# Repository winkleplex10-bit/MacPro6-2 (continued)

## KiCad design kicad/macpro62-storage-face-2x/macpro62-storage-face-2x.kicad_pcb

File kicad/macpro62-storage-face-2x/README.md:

# macpro62-storage-face-2x (S2X rev A0): Face S module, 2 x M.2 2280, switchless
Replaces the parked 4-drive ASM2824 board (`../macpro62-storage-face`, SM-1) for the first build. Same outline, holes, J1 MCIO 124 at X 47.0 and bus-bar lugs.

- J1 x8 → x4 slot A (lanes 0-3, REFCLK0/PERST0#) + x4 slot B (lanes 4-7, REFCLK1/PERST1#). Slot B needs host changes: `docs/ICD_CHANGES.md`.
- M.2 M-key: LOTES APCI0107-P001A (LCSC C841661) + SMTSO2030CTJ standoffs (2280).
- Power: TPS259470 eFuse, INA238 (0x40), 2 x TPS54331 buck (3 A per slot), TMP1075 0x48/0x49, M24C64 0x50, activity LEDs D3/D4.
- 4L JLC04161H-7628, 85 Ω pairs; all parts on B (JLC Economic, single-sided).

Checks (2026-10-08): DRC 0 / unconnected 0 / schematic parity 0 (kicad-cli, all severities), ERC 0 (`erc_report.txt`).
Fab/assembly: `jlc/` (gerbers zip, BOM 36 lines, CPL 81 parts, all Bottom). Previews: `docs/preview_2X_*.png`. Log: `PROGRESS.md`.
Deviations D-2X-1 (hot spot), D-2X-2 (data-lane polarity inversion), D-S1 (no X-bracket): `docs/ICD_CHANGES.md`.

Rebuild: tools/model.py → build_pcb.py → route_hs.py → route_pwr.py → s2x_ls.py fan → Freerouting (10 min) → s2x_ls.py import →
s2x_clean.py (loop) → s2x_finish.py → tools/drc.sh; schematic: build_sch.py.

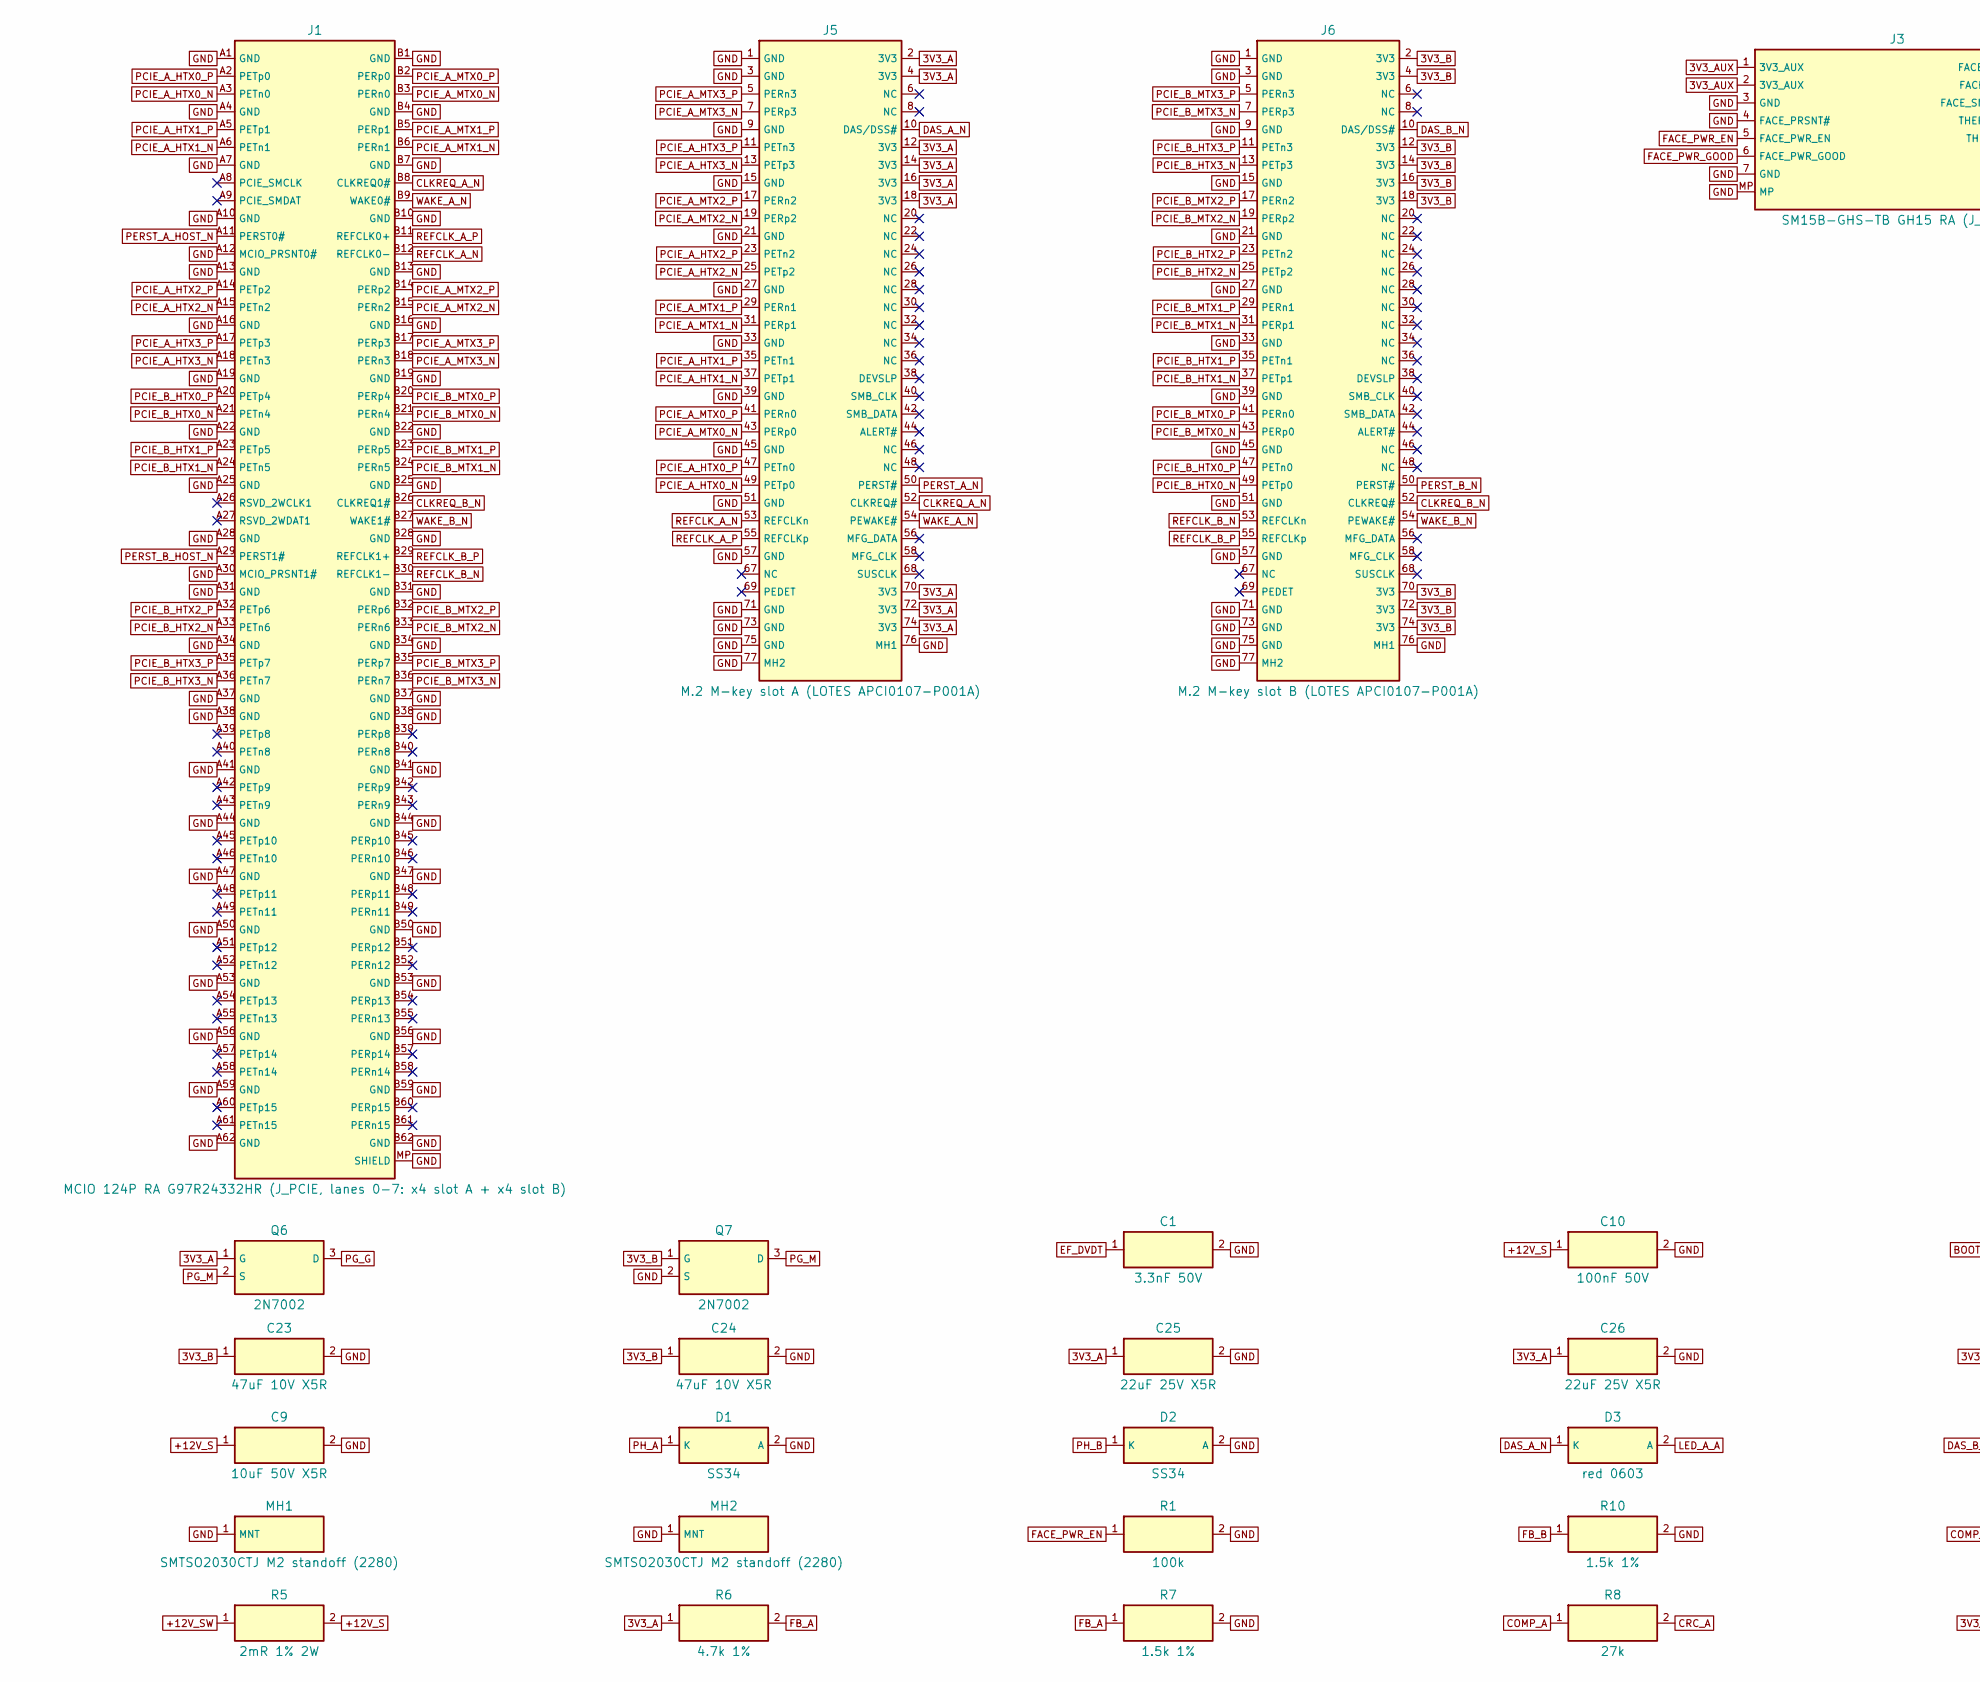
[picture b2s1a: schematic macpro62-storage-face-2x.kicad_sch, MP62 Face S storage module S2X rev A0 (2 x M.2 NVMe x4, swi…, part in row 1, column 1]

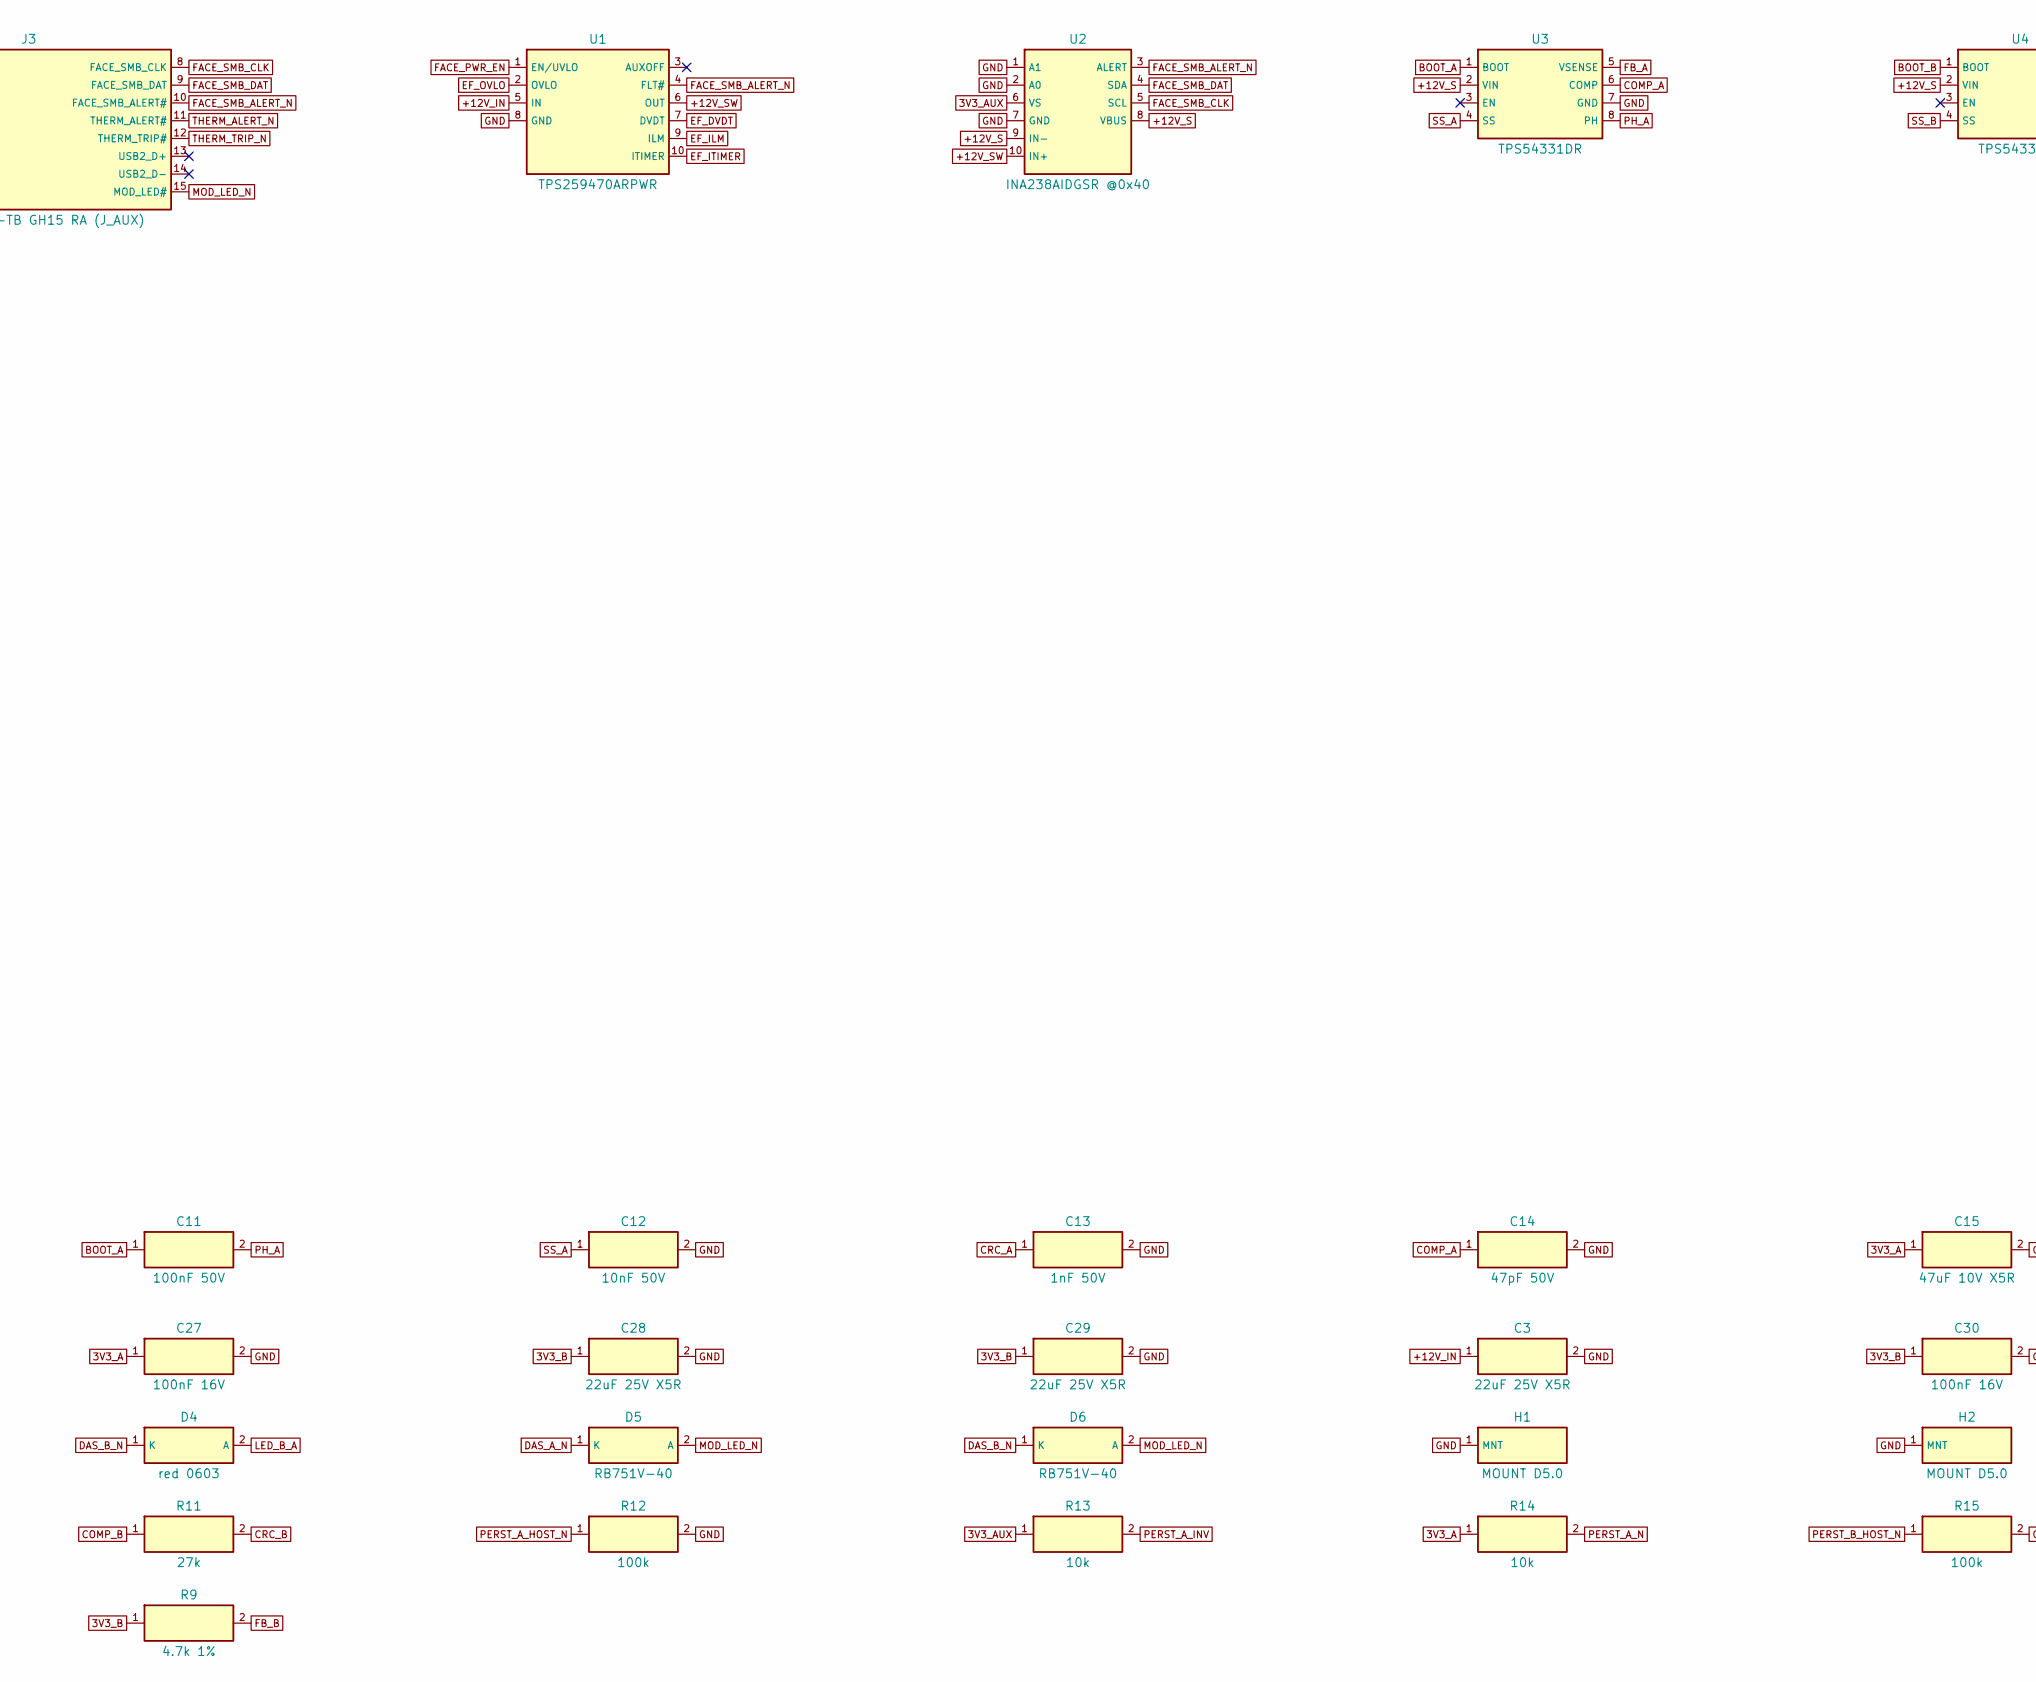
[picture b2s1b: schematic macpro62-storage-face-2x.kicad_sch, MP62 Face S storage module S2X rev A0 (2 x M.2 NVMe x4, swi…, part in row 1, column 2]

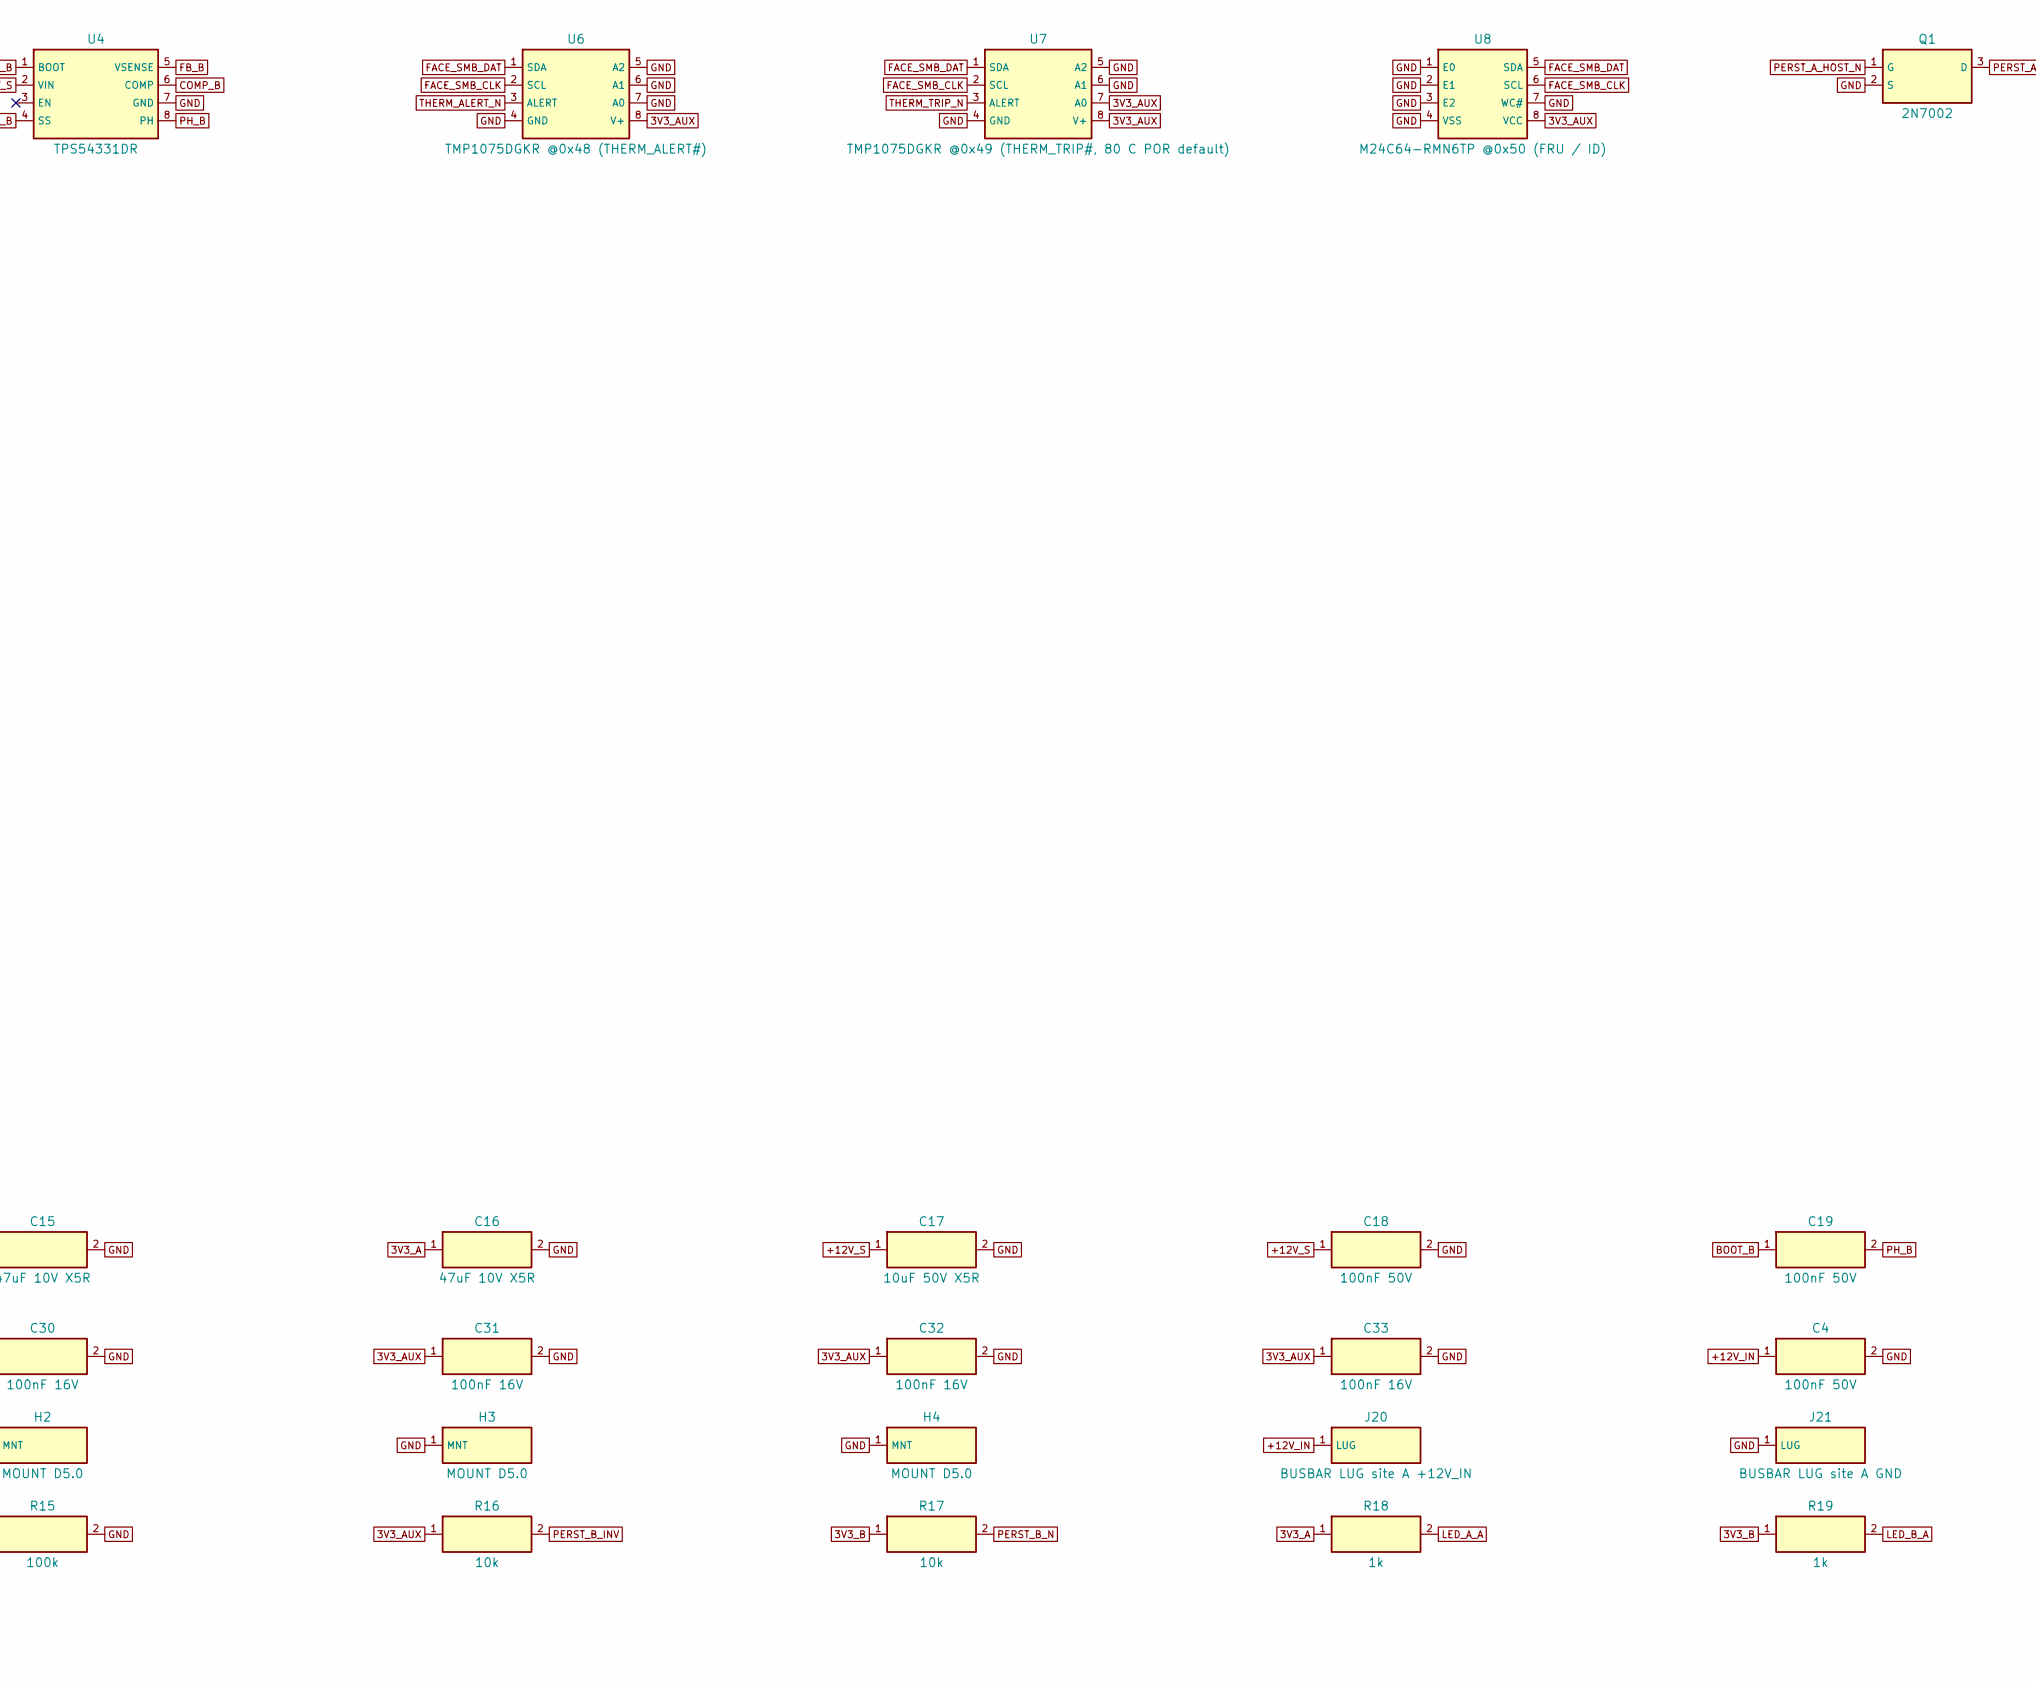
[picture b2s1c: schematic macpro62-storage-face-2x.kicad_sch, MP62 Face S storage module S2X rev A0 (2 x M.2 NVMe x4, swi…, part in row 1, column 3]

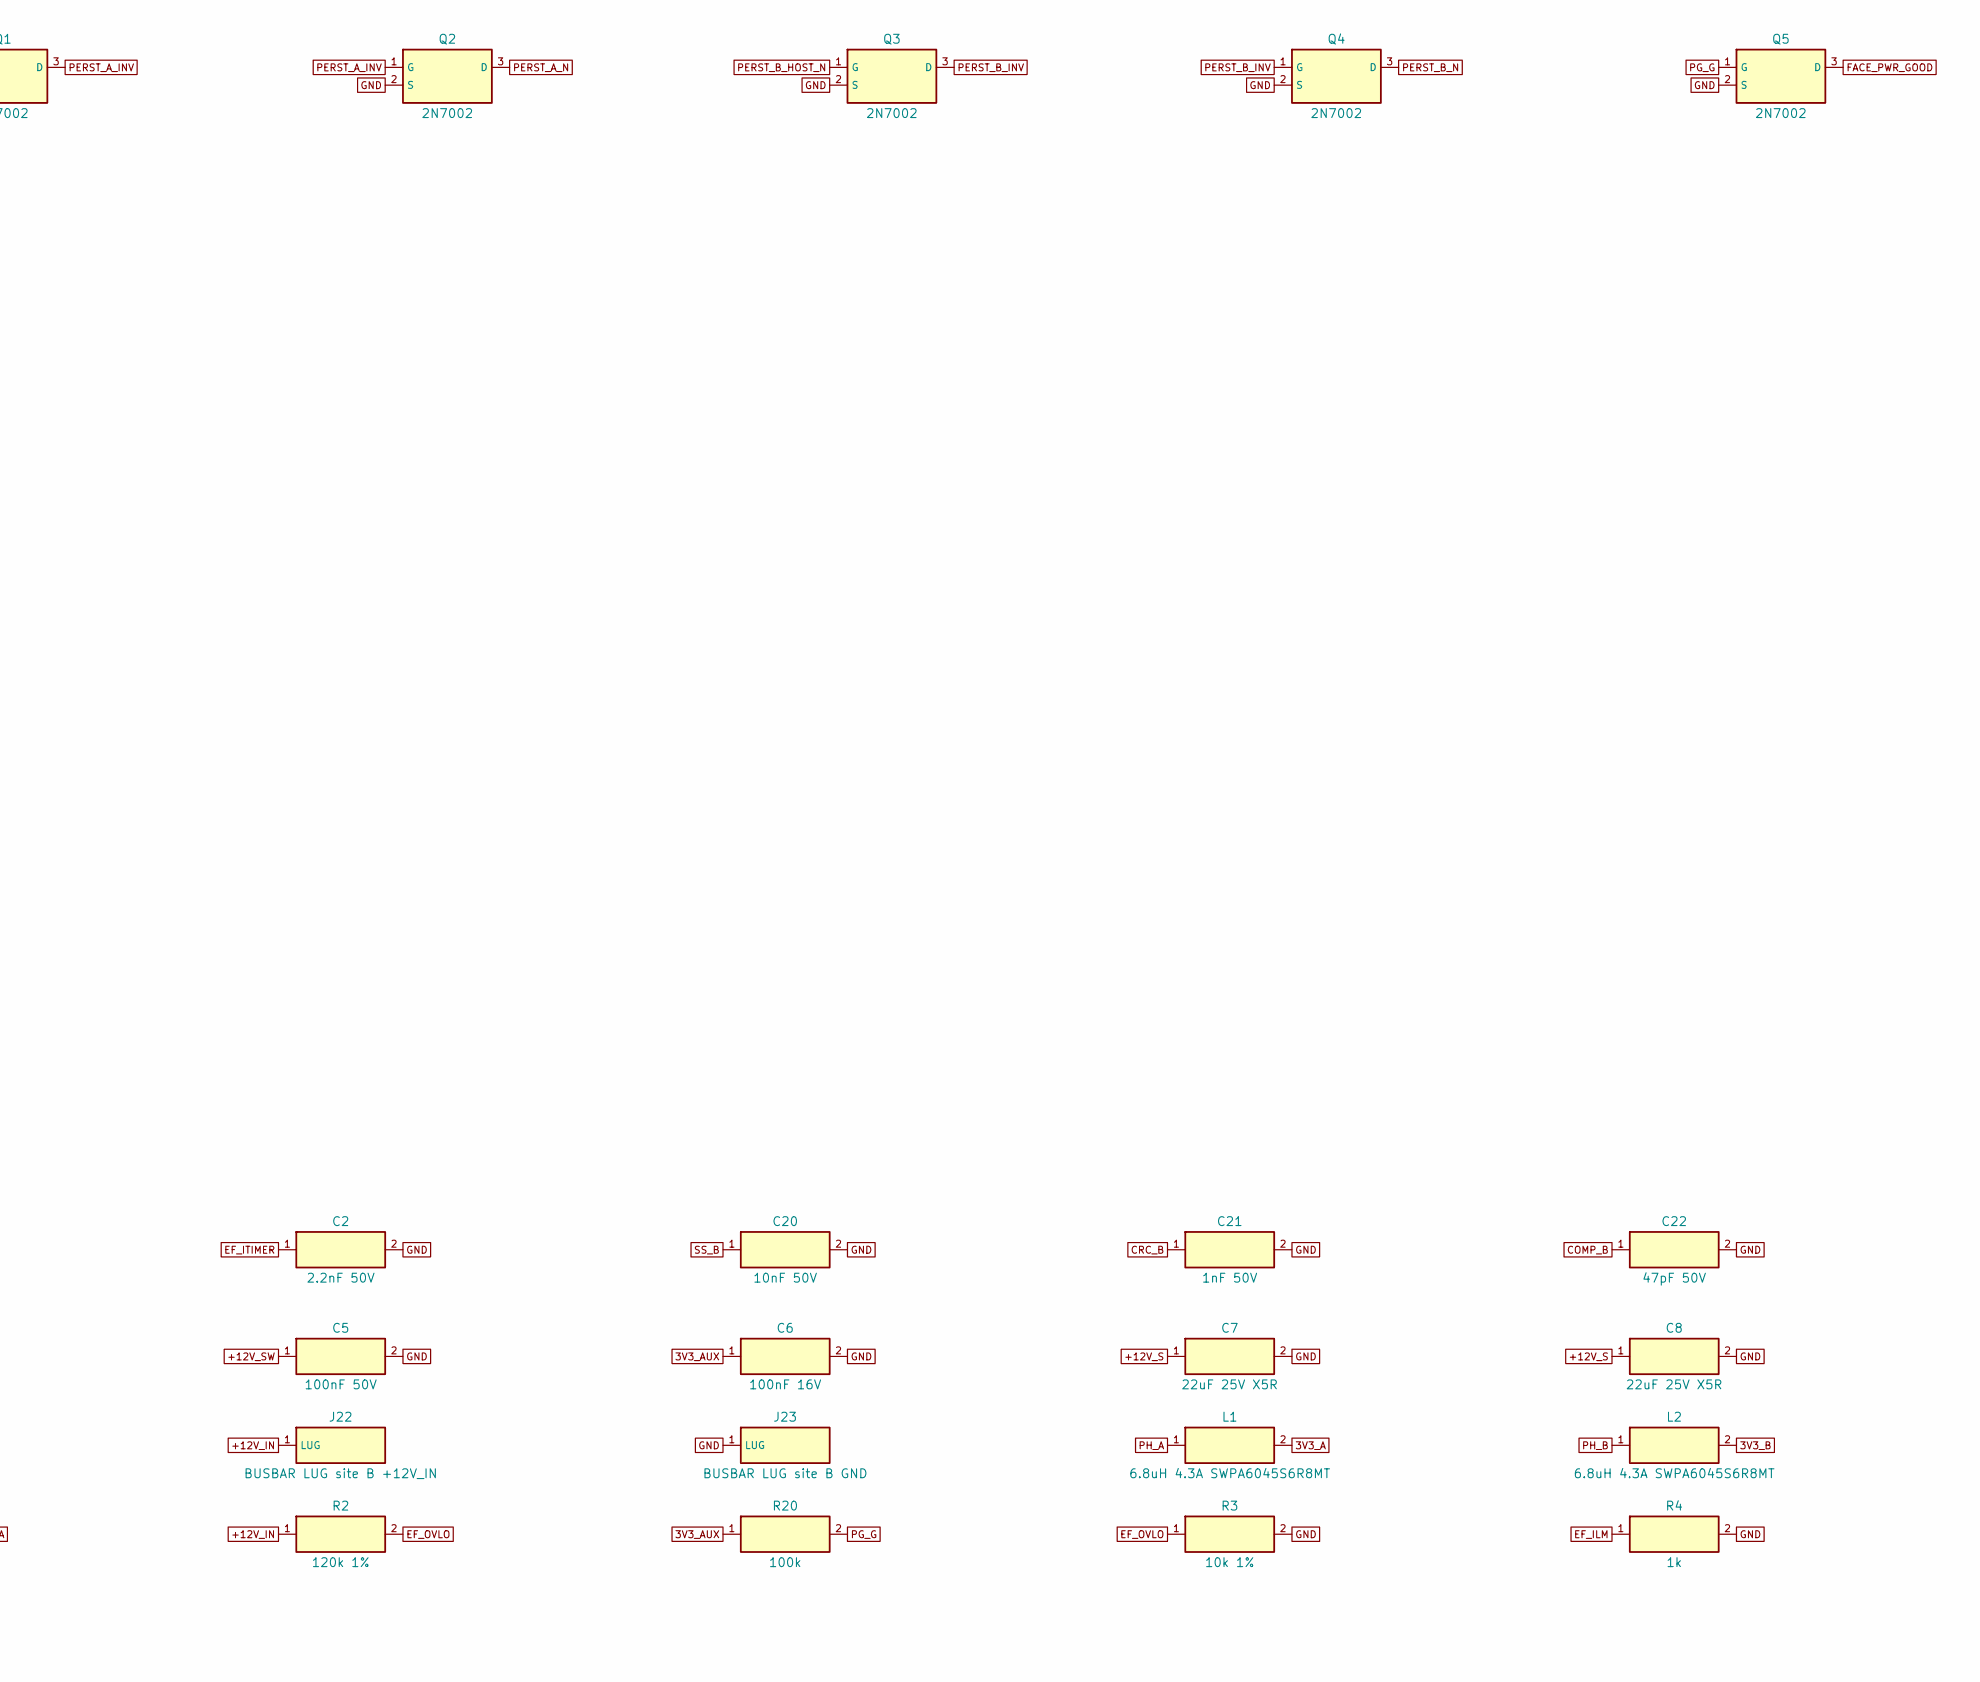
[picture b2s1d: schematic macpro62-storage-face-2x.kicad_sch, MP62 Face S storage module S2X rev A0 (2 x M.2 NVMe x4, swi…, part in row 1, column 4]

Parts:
C1: 3.3nF 50V; C_0402_1005Metric; LCSC C26404
C2: 2.2nF 50V; C_0402_1005Metric; LCSC C1531
C3, C7, C8: 22uF 25V X5R; C_1206_3216Metric; LCSC C12891
C4, C5, C10, C11, C18, C19: 100nF 50V; C_0402_1005Metric; LCSC C307331
C6, C27, C30, C31, C32, C33: 100nF 16V; C_0402_1005Metric; LCSC C1525
C9, C17: 10uF 50V X5R; C_1206_3216Metric; LCSC C13585
C12, C20: 10nF 50V; C_0402_1005Metric; LCSC C15195
C13, C21: 1nF 50V; C_0402_1005Metric; LCSC C1523
C14, C22: 47pF 50V; C_0402_1005Metric; LCSC C1567
C15, C16, C23, C24: 47uF 10V X5R; C_1206_3216Metric; LCSC C96123
C25, C26, C28, C29: 22uF 25V X5R; C_0805_2012Metric; LCSC C45783
D1, D2: SS34; D_SMA; LCSC C8678
D3, D4: red 0603; LED_0603_1608Metric; LCSC C2286
D5, D6: RB751V-40; D_SOD-323; LCSC C7502691
H1, H2, H3, H4: MOUNT D5.0; MP62_FACE_MountHole_D5.0_Pad9.0
J1: MCIO 124P RA G97R24332HR (J_PCIE, lanes 0-7: x4 s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; MP62_MCIO_124P_RA_SFF-TA-1016; LCSC C4867471
J3: SM15B-GHS-TB GH15 RA (J_AUX); JST_GH_SM15B-GHS-TB_1x15-1MP_P1.25mm_Horizontal; LCSC C265027
J5: M.2 M-key slot A (LOTES APCI0107-P001A); M2_M-Key_LOTES_APCI0107-P001A; LCSC C841661
J6: M.2 M-key slot B (LOTES APCI0107-P001A); M2_M-Key_LOTES_APCI0107-P001A; LCSC C841661
J20: BUSBAR LUG site A +12V_IN; MP62_FACE_BusBarLug_D3.2_Pad8.8
J21: BUSBAR LUG site A GND; MP62_FACE_BusBarLug_D3.2_Pad8.8
J22: BUSBAR LUG site B +12V_IN; MP62_FACE_BusBarLug_D3.2_Pad8.8
J23: BUSBAR LUG site B GND; MP62_FACE_BusBarLug_D3.2_Pad8.8
L1, L2: 6.8uH 4.3A SWPA6045S6R8MT; L_Sunlord_SWPA6045S; LCSC C57254
MH1, MH2: SMTSO2030CTJ M2 standoff (2280); M2_Standoff_SMTSO2030CTJ_M2_H3.0; LCSC C2915627
Q1, Q2, Q3, Q4, Q5, Q6, Q7: 2N7002; SOT-23; LCSC C8545
R1, R12, R15, R20: 100k; R_0402_1005Metric; LCSC C25741
R2: 120k 1%; R_0603_1608Metric; LCSC C25808
R3: 10k 1%; R_0402_1005Metric; LCSC C25744
R4, R18, R19: 1k; R_0402_1005Metric; LCSC C11702
R5: 2mR 1% 2W; R_2512_6332Metric; LCSC C160926
R6, R9: 4.7k 1%; R_0402_1005Metric; LCSC C25900
R7, R10: 1.5k 1%; R_0402_1005Metric; LCSC C25867
R8, R11: 27k; R_0402_1005Metric; LCSC C25771
R13, R14, R16, R17: 10k; R_0402_1005Metric; LCSC C25744
U1: TPS259470ARPWR; TI_RPW_VQFN-10_2x2mm_P0.45mm; LCSC C3662799
U2: INA238AIDGSR @0x40; VSSOP-10_3x3mm_P0.5mm; LCSC C2868250
U3, U4: TPS54331DR; SOIC-8_3.9x4.9mm_P1.27mm; LCSC C9865
U6: TMP1075DGKR @0x48 (THERM_ALERT#); VSSOP-8_3x3mm_P0.65mm; LCSC C2864807
U7: TMP1075DGKR @0x49 (THERM_TRIP#, 80 C POR default); VSSOP-8_3x3mm_P0.65mm; LCSC C2864807
U8: M24C64-RMN6TP @0x50 (FRU / ID); SOIC-8_3.9x4.9mm_P1.27mm; LCSC C79988

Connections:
3V3_A: C15.1, C16.1, C25.1, C26.1, C27.1, J5.2 (3V3), J5.4 (3V3), J5.12 (3V3), J5.14 (3V3), J5.16 (3V3), J5.18 (3V3), J5.70 (3V3), J5.72 (3V3), J5.74 (3V3), L1.2, Q6.1 (G), R6.1, R14.1, R18.1
3V3_AUX: C6.1, C31.1, C32.1, C33.1, J3.1 (3V3_AUX), J3.2 (3V3_AUX), R13.1, R16.1, R20.1, U2.6 (VS), U6.8 (V+), U7.7 (A0), U7.8 (V+), U8.8 (VCC)
3V3_B: C23.1, C24.1, C28.1, C29.1, C30.1, J6.2 (3V3), J6.4 (3V3), J6.12 (3V3), J6.14 (3V3), J6.16 (3V3), J6.18 (3V3), J6.70 (3V3), J6.72 (3V3), J6.74 (3V3), L2.2, Q7.1 (G), R9.1, R17.1, R19.1
+12V_IN: C3.1, C4.1, J20.1, J22.1, R2.1, U1.5 (IN)
+12V_S: C7.1, C8.1, C9.1, C10.1, C17.1, C18.1, R5.2, U2.8 (VBUS), U2.9 (IN-), U3.2 (VIN), U4.2 (VIN)
+12V_SW: C5.1, R5.1, U1.6 (OUT), U2.10 (IN+)
BOOT_A: C11.1, U3.1 (BOOT)
BOOT_B: C19.1, U4.1 (BOOT)
CLKREQ_A_N: J1.B8 (CLKREQ0#), J5.52 (CLKREQ#)
CLKREQ_B_N: J1.B26 (CLKREQ1#), J6.52 (CLKREQ#)
COMP_A: C14.1, R8.1, U3.6 (COMP)
COMP_B: C22.1, R11.1, U4.6 (COMP)
CRC_A: C13.1, R8.2
CRC_B: C21.1, R11.2
DAS_A_N: D3.1 (K), D5.1 (K), J5.10 (DAS/DSS#)
DAS_B_N: D4.1 (K), D6.1 (K), J6.10 (DAS/DSS#)
EF_DVDT: C1.1, U1.7 (DVDT)
EF_ILM: R4.1, U1.9 (ILM)
EF_ITIMER: C2.1, U1.10 (ITIMER)
EF_OVLO: R2.2, R3.1, U1.2 (OVLO)
FACE_PWR_EN: J3.5 (FACE_PWR_EN), R1.1, U1.1 (EN/UVLO)
FACE_PWR_GOOD: J3.6 (FACE_PWR_GOOD), Q5.3 (D)
FACE_SMB_ALERT_N: J3.10 (FACE_SMB_ALERT#), U1.4 (FLT#), U2.3 (ALERT)
FACE_SMB_CLK: J3.8 (FACE_SMB_CLK), U2.5 (SCL), U6.2 (SCL), U7.2 (SCL), U8.6 (SCL)
FACE_SMB_DAT: J3.9 (FACE_SMB_DAT), U2.4 (SDA), U6.1 (SDA), U7.1 (SDA), U8.5 (SDA)
FB_A: R6.2, R7.1, U3.5 (VSENSE)
FB_B: R9.2, R10.1, U4.5 (VSENSE)
GND: C1.2, C2.2, C3.2, C4.2, C5.2, C6.2, C7.2, C8.2, C9.2, C10.2, C12.2, C13.2, C14.2, C15.2, C16.2, C17.2, C18.2, C20.2, C21.2, C22.2, C23.2, C24.2, C25.2, C26.2, C27.2, C28.2, C29.2, C30.2, C31.2, C32.2, C33.2, D1.2 (A), D2.2 (A), H1.1, H2.1, H3.1, H4.1, J1.A1 (GND), J1.A4 (GND), J1.A7 (GND), J1.A10 (GND), J1.A12 (MCIO_PRSNT0#), J1.A13 (GND), J1.A16 (GND), J1.A19 (GND), J1.A22 (GND), J1.A25 (GND), J1.A28 (GND), J1.A30 (MCIO_PRSNT1#), J1.A31 (GND), J1.A34 (GND), J1.A37 (GND), J1.A38 (GND), J1.A41 (GND), J1.A44 (GND), J1.A47 (GND), J1.A50 (GND), J1.A53 (GND), J1.A56 (GND), J1.A59 (GND), J1.A62 (GND), J1.B1 (GND), J1.B4 (GND), J1.B7 (GND), J1.B10 (GND), J1.B13 (GND), J1.B16 (GND), J1.B19 (GND), J1.B22 (GND), J1.B25 (GND), J1.B28 (GND), J1.B31 (GND), J1.B34 (GND), J1.B37 (GND), J1.B38 (GND), J1.B41 (GND), J1.B44 (GND), J1.B47 (GND), J1.B50 (GND), J1.B53 (GND), J1.B56 (GND), J1.B59 (GND), J1.B62 (GND), J1.MP (SHIELD), J3.3 (GND), J3.4 (FACE_PRSNT#), J3.7 (GND), J3.MP, J5.1 (GND), J5.3 (GND), J5.9 (GND), J5.15 (GND), J5.21 (GND), J5.27 (GND), J5.33 (GND), J5.39 (GND), J5.45 (GND), J5.51 (GND), J5.57 (GND), J5.71 (GND), J5.73 (GND), J5.75 (GND), J5.76 (MH1), J5.77 (MH2), J6.1 (GND), J6.3 (GND), J6.9 (GND), J6.15 (GND), J6.21 (GND), J6.27 (GND), J6.33 (GND), J6.39 (GND), J6.45 (GND), J6.51 (GND), J6.57 (GND), J6.71 (GND), J6.73 (GND), J6.75 (GND), J6.76 (MH1), J6.77 (MH2), J21.1, J23.1, MH1.1, MH2.1, Q1.2 (S), Q2.2 (S), Q3.2 (S), Q4.2 (S), Q5.2 (S), Q7.2 (S), R1.2, R3.2, R4.2, R7.2, R10.2, R12.2, R15.2, U1.8 (GND), U2.1 (A1), U2.2 (A0), U2.7 (GND), U3.7 (GND), U4.7 (GND), U6.4 (GND), U6.5 (A2), U6.6 (A1), U6.7 (A0), U7.4 (GND), U7.5 (A2), U7.6 (A1), U8.1 (E0), U8.2 (E1), U8.3 (E2), U8.4 (VSS), U8.7 (WC#)
LED_A_A: D3.2 (A), R18.2
LED_B_A: D4.2 (A), R19.2
MOD_LED_N: D5.2 (A), D6.2 (A), J3.15 (MOD_LED#)
PCIE_A_HTX0_N: J1.A3 (PETn0), J5.49 (PETp0)
PCIE_A_HTX0_P: J1.A2 (PETp0), J5.47 (PETn0)
PCIE_A_HTX1_N: J1.A6 (PETn1), J5.37 (PETp1)
PCIE_A_HTX1_P: J1.A5 (PETp1), J5.35 (PETn1)
PCIE_A_HTX2_N: J1.A15 (PETn2), J5.25 (PETp2)
PCIE_A_HTX2_P: J1.A14 (PETp2), J5.23 (PETn2)
PCIE_A_HTX3_N: J1.A18 (PETn3), J5.13 (PETp3)
PCIE_A_HTX3_P: J1.A17 (PETp3), J5.11 (PETn3)
PCIE_A_MTX0_N: J1.B3 (PERn0), J5.43 (PERp0)
PCIE_A_MTX0_P: J1.B2 (PERp0), J5.41 (PERn0)
PCIE_A_MTX1_N: J1.B6 (PERn1), J5.31 (PERp1)
PCIE_A_MTX1_P: J1.B5 (PERp1), J5.29 (PERn1)
PCIE_A_MTX2_N: J1.B15 (PERn2), J5.19 (PERp2)
PCIE_A_MTX2_P: J1.B14 (PERp2), J5.17 (PERn2)
PCIE_A_MTX3_N: J1.B18 (PERn3), J5.7 (PERp3)
PCIE_A_MTX3_P: J1.B17 (PERp3), J5.5 (PERn3)
PCIE_B_HTX0_N: J1.A21 (PETn4), J6.49 (PETp0)
PCIE_B_HTX0_P: J1.A20 (PETp4), J6.47 (PETn0)
PCIE_B_HTX1_N: J1.A24 (PETn5), J6.37 (PETp1)
PCIE_B_HTX1_P: J1.A23 (PETp5), J6.35 (PETn1)
PCIE_B_HTX2_N: J1.A33 (PETn6), J6.25 (PETp2)
PCIE_B_HTX2_P: J1.A32 (PETp6), J6.23 (PETn2)
PCIE_B_HTX3_N: J1.A36 (PETn7), J6.13 (PETp3)
PCIE_B_HTX3_P: J1.A35 (PETp7), J6.11 (PETn3)
PCIE_B_MTX0_N: J1.B21 (PERn4), J6.43 (PERp0)
PCIE_B_MTX0_P: J1.B20 (PERp4), J6.41 (PERn0)
PCIE_B_MTX1_N: J1.B24 (PERn5), J6.31 (PERp1)
PCIE_B_MTX1_P: J1.B23 (PERp5), J6.29 (PERn1)
PCIE_B_MTX2_N: J1.B33 (PERn6), J6.19 (PERp2)
PCIE_B_MTX2_P: J1.B32 (PERp6), J6.17 (PERn2)
PCIE_B_MTX3_N: J1.B36 (PERn7), J6.7 (PERp3)
PCIE_B_MTX3_P: J1.B35 (PERp7), J6.5 (PERn3)
PERST_A_HOST_N: J1.A11 (PERST0#), Q1.1 (G), R12.1
PERST_A_INV: Q1.3 (D), Q2.1 (G), R13.2
PERST_A_N: J5.50 (PERST#), Q2.3 (D), R14.2
PERST_B_HOST_N: J1.A29 (PERST1#), Q3.1 (G), R15.1
PERST_B_INV: Q3.3 (D), Q4.1 (G), R16.2
PERST_B_N: J6.50 (PERST#), Q4.3 (D), R17.2
PG_G: Q5.1 (G), Q6.3 (D), R20.2
PG_M: Q6.2 (S), Q7.3 (D)
PH_A: C11.2, D1.1 (K), L1.1, U3.8 (PH)
PH_B: C19.2, D2.1 (K), L2.1, U4.8 (PH)
REFCLK_A_N: J1.B12 (REFCLK0-), J5.53 (REFCLKn)
REFCLK_A_P: J1.B11 (REFCLK0+), J5.55 (REFCLKp)
REFCLK_B_N: J1.B30 (REFCLK1-), J6.53 (REFCLKn)
REFCLK_B_P: J1.B29 (REFCLK1+), J6.55 (REFCLKp)
SS_A: C12.1, U3.4 (SS)
SS_B: C20.1, U4.4 (SS)
THERM_ALERT_N: J3.11 (THERM_ALERT#), U6.3 (ALERT)
THERM_TRIP_N: J3.12 (THERM_TRIP#), U7.3 (ALERT)
WAKE_A_N: J1.B9 (WAKE0#), J5.54 (PEWAKE#)
WAKE_B_N: J1.B27 (WAKE1#), J6.54 (PEWAKE#)

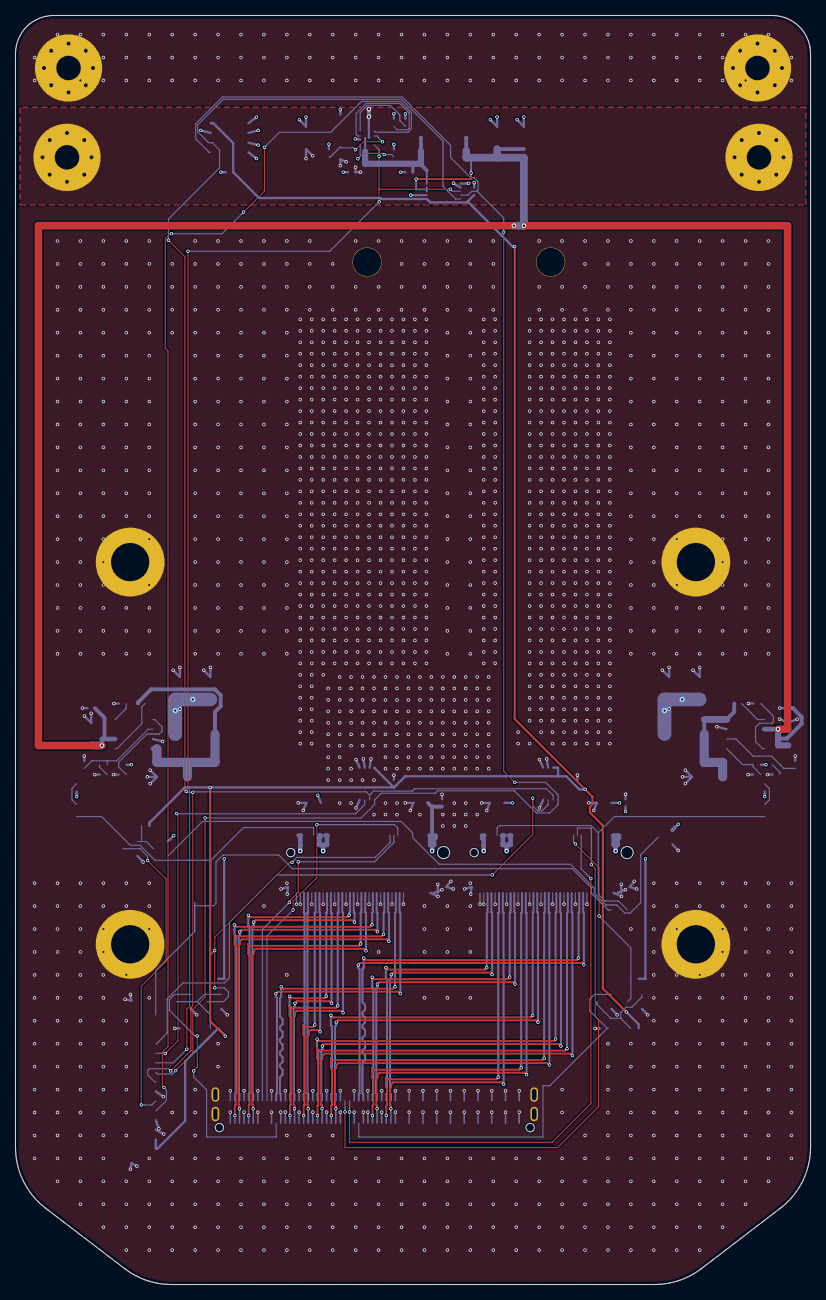
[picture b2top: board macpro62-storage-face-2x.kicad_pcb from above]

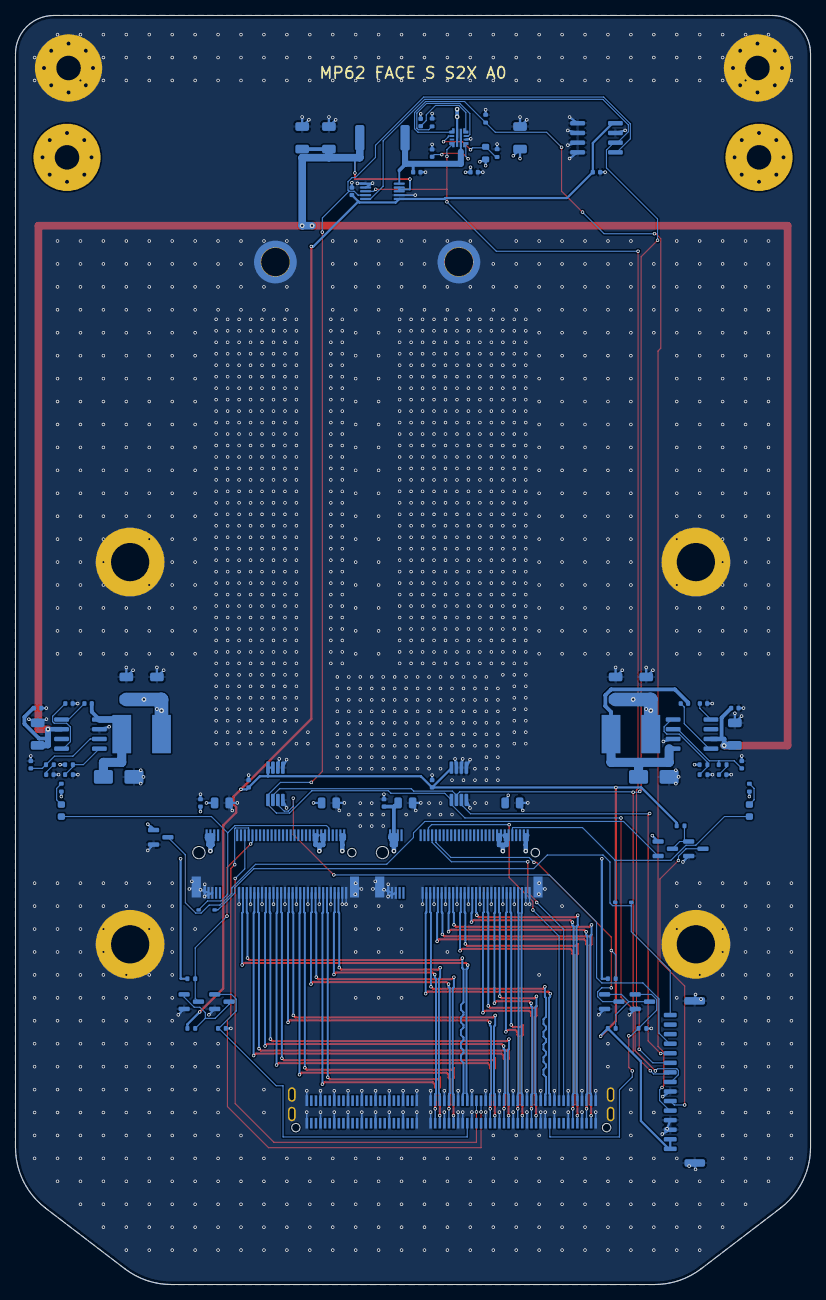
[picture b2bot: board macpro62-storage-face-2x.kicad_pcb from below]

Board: 4 copper layers, 104.0 x 166.0 mm, 89 parts (81 on the bottom side), 83 nets.

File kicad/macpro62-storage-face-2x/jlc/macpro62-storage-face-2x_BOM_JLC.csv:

Comment,Designator,Footprint,LCSC Part #
3.3nF 50V,C1,C_0402_1005Metric,C26404
100nF 50V,"C10,C11,C18,C19,C4,C5",C_0402_1005Metric,C307331
10nF 50V,"C12,C20",C_0402_1005Metric,C15195
1nF 50V,"C13,C21",C_0402_1005Metric,C1523
47pF 50V,"C14,C22",C_0402_1005Metric,C1567
47uF 10V X5R,"C15,C16,C23,C24",C_1206_3216Metric,C96123
10uF 50V X5R,"C17,C9",C_1206_3216Metric,C13585
2.2nF 50V,C2,C_0402_1005Metric,C1531
22uF 25V X5R,"C25,C26,C28,C29",C_0805_2012Metric,C45783
100nF 16V,"C27,C30,C31,C32,C33,C6",C_0402_1005Metric,C1525
22uF 25V X5R,"C3,C7,C8",C_1206_3216Metric,C12891
SS34,"D1,D2",D_SMA,C8678
red 0603,"D3,D4",LED_0603_1608Metric,C2286
RB751V-40,"D5,D6",D_SOD-323,C7502691
"MCIO 124P RA G97R24332HR (J_PCIE, lanes 0-7: x4 slot A + x4 slot B)",J1,MP62_MCIO_124P_RA_SFF-TA-1016,C4867471
SM15B-GHS-TB GH15 RA (J_AUX),J3,JST_GH_SM15B-GHS-TB_1x15-1MP_P1.25mm_Horizontal,C265027
M.2 M-key slot A (LOTES APCI0107-P001A),J5,M2_M-Key_LOTES_APCI0107-P001A,C841661
M.2 M-key slot B (LOTES APCI0107-P001A),J6,M2_M-Key_LOTES_APCI0107-P001A,C841661
6.8uH 4.3A SWPA6045S6R8MT,"L1,L2",L_Sunlord_SWPA6045S,C57254
SMTSO2030CTJ M2 standoff (2280),"MH1,MH2",M2_Standoff_SMTSO2030CTJ_M2_H3.0,C2915627
2N7002,"Q1,Q2,Q3,Q4,Q5,Q6,Q7",SOT-23,C8545
100k,"R1,R12,R15,R20",R_0402_1005Metric,C25741
1.5k 1%,"R10,R7",R_0402_1005Metric,C25867
27k,"R11,R8",R_0402_1005Metric,C25771
10k,"R13,R14,R16,R17",R_0402_1005Metric,C25744
1k,"R18,R19,R4",R_0402_1005Metric,C11702
120k 1%,R2,R_0603_1608Metric,C25808
10k 1%,R3,R_0402_1005Metric,C25744
2mR 1% 2W,R5,R_2512_6332Metric,C160926
4.7k 1%,"R6,R9",R_0402_1005Metric,C25900
TPS259470ARPWR,U1,TI_RPW_VQFN-10_2x2mm_P0.45mm,C3662799
INA238AIDGSR @0x40,U2,VSSOP-10_3x3mm_P0.5mm,C2868250
TPS54331DR,"U3,U4",SOIC-8_3.9x4.9mm_P1.27mm,C9865
TMP1075DGKR @0x48 (THERM_ALERT#),U6,VSSOP-8_3x3mm_P0.65mm,C2864807
"TMP1075DGKR @0x49 (THERM_TRIP#, 80 C POR default)",U7,VSSOP-8_3x3mm_P0.65mm,C2864807
M24C64-RMN6TP @0x50 (FRU / ID),U8,SOIC-8_3.9x4.9mm_P1.27mm,C79988
